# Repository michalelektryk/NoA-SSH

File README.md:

# Noise of Antimatter - Subshaper
## disclaimer
This repository contains all files required to make or repair the SSH. The following files are provided as is, with no responsibility. They're provided for personal use only. If you'd like to sell anything made out of them feel free to ping me, I'm mostly ok, as long as you're not big company scamming small manufacturers :)
## Module description
SSH is 16HP triple waveshaper with subharmonicon and sequencer. It's versatile tool for enriching sound sources and animating voices. More information can be found on [the webpage](https://noiseofantimatter.com/modules/ssh_module/) or by checking out [the demo](https://www.youtube.com/watch?v=Nd7Cz19s0W0).

## File structure
- electronics design can be found in folder [electronics](/electronics)
  - schematic.pdf is useful for quick look. For editing and deep dive full kicad design is provided. Project was done in kicad 6 but seems to work equally well in 7/8
- CPDL firmware is provided in folder [greenpak](/greenpak)
  - the device hides all complex digital logic into two greenpak CPLDs.
  - Their configuration and ESP32 software used for flashing are here
- panel design can be found in folder [panel](/panel)
  - panel has been designed as 3d model in openSCAD. Two projections are available for CNC production. Additionally, stls for dual color printing are provided
- manual generating files and pdf can be found in [manual](/manual)
  - It's written in LaTeX. For people who don't know LaTeX I recommend you read about it, especially if you're doing group projects and need to git proper documents

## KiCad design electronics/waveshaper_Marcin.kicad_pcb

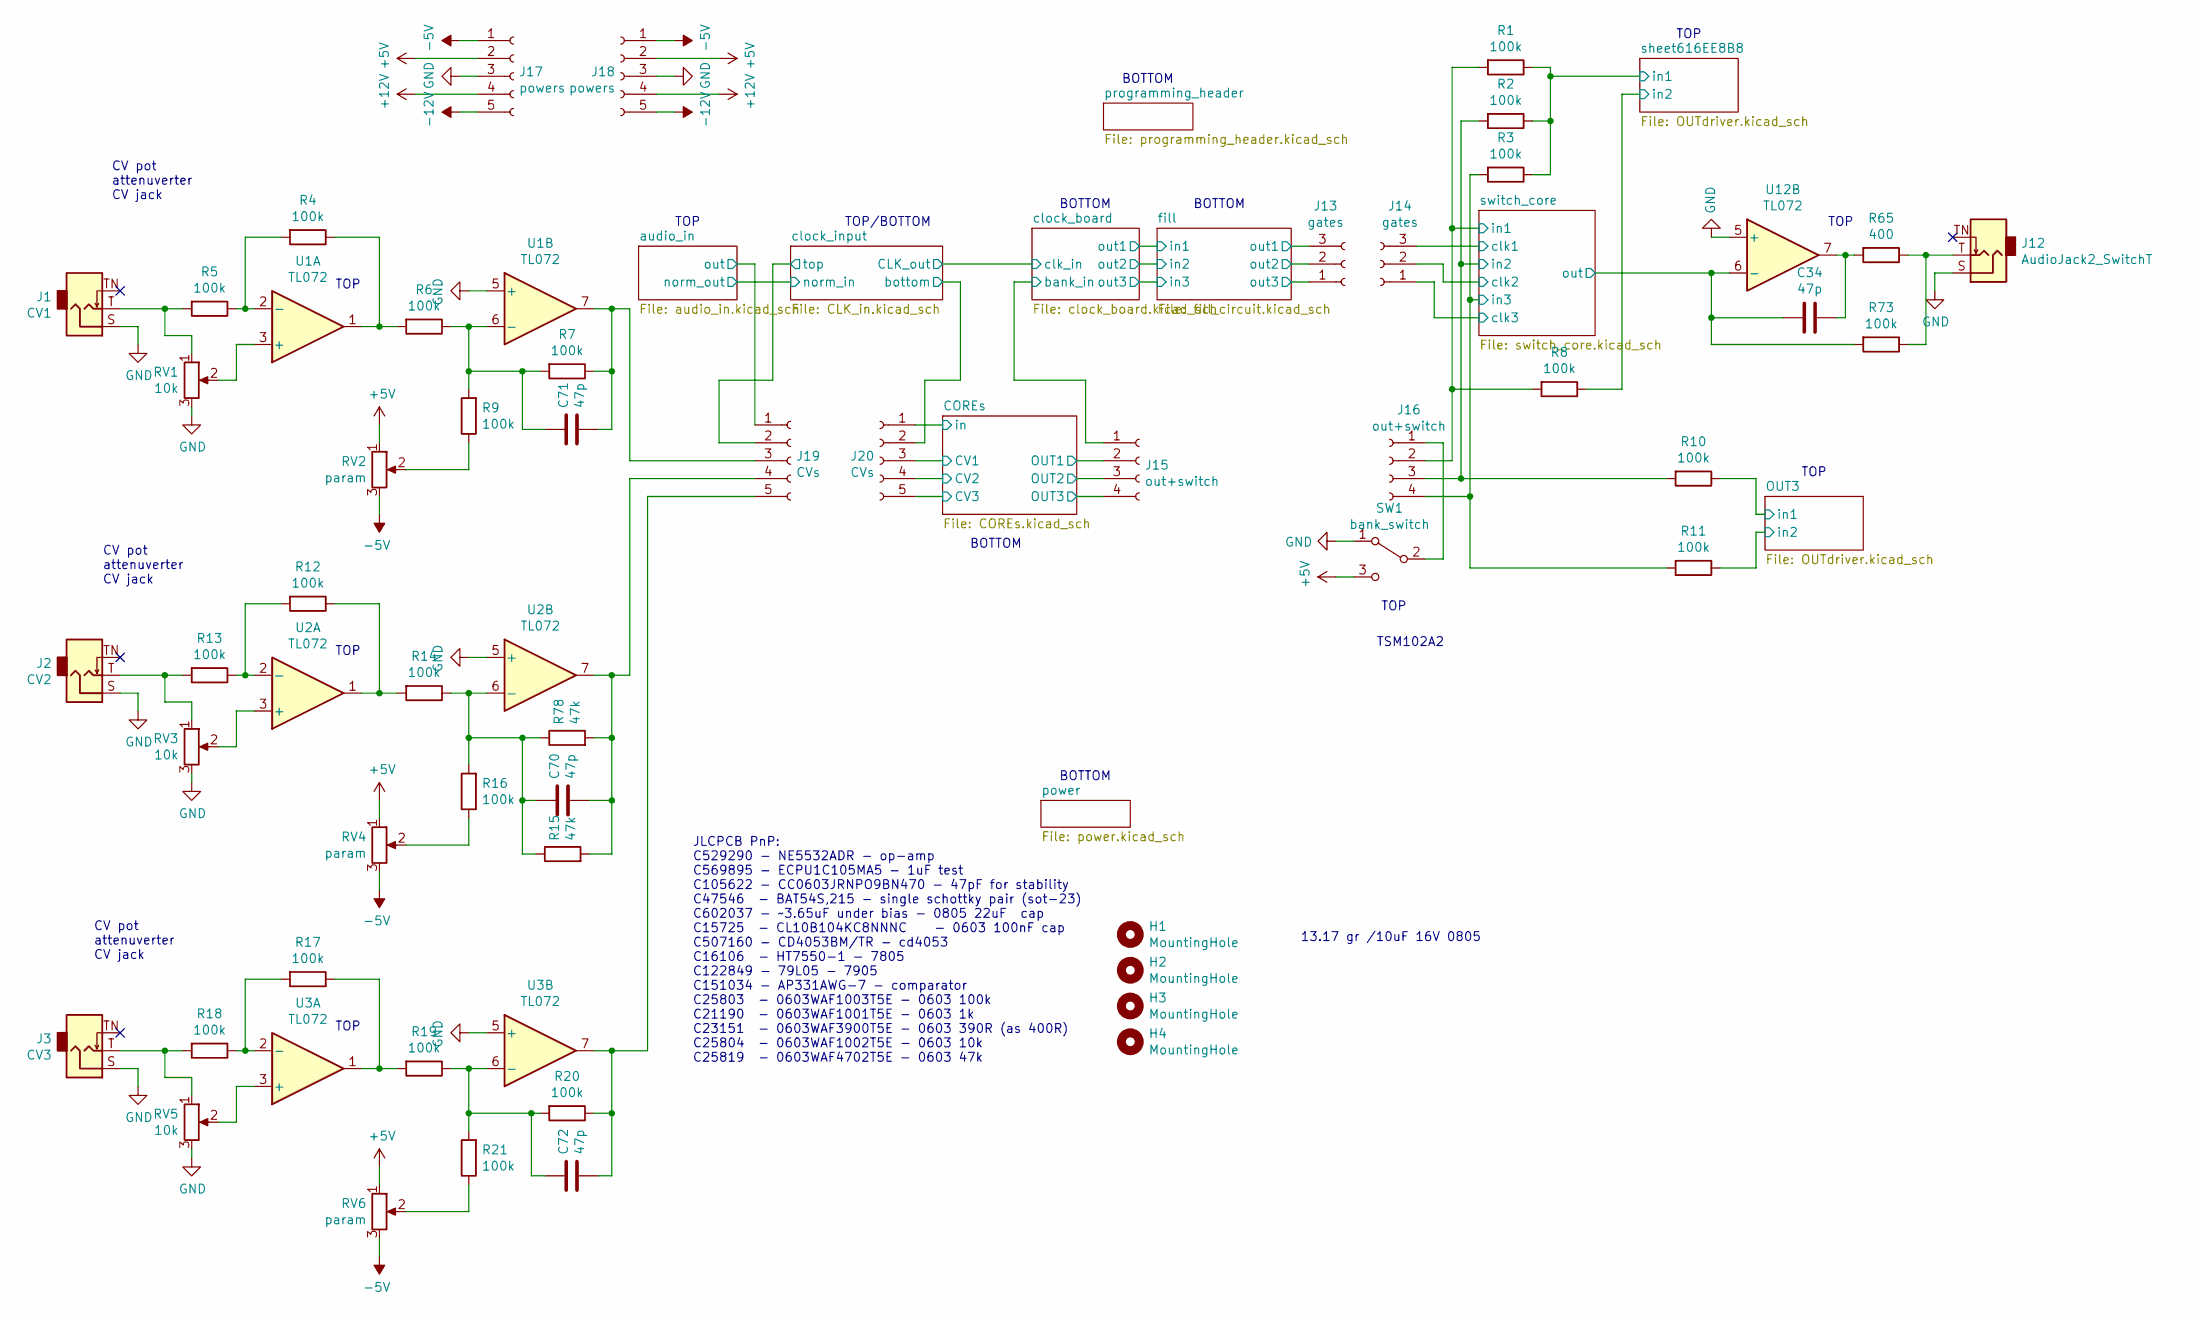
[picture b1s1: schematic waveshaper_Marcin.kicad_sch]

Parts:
C34, C70, C71, C72: 47p; C_0603_1608Metric
H1, H2, H3, H4: MountingHole; SS-16F03_cutout
J1: CV1; thonkiconn
J2: CV2; thonkiconn
J3: CV3; thonkiconn
J12: AudioJack2_SwitchT; thonkiconn
J13, J14: gates; PinHeader_1x03_P2.54mm_Vertical
J15, J16: out+switch; PinHeader_1x04_P2.54mm_Vertical
J17, J18: powers; PinHeader_1x05_P2.54mm_Vertical
J19, J20: CVs; PinHeader_1x05_P2.54mm_Vertical
R1, R2, R3, R4, R5, R6, R7, R8, R9, R10, R11, R12, R13, R14, R16, R17, R18, R19, R20, R21, R73: 100k; R_0603_1608Metric
R15, R78: 47k; R_0603_1608Metric
R65: 400; R_0603_1608Metric
RV1, RV3, RV5: 10k; Potentiometer_Alps_RK09K_Single_Vertical
RV2, RV4, RV6: param; Potentiometer_Alps_RK09K_Single_Vertical
SW1: bank_switch; TSM1x3
U1, U2, U3, U12: TL072; SOIC-8_3.9x4.9mm_P1.27mm

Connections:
+5V: J17.2, J18.2, RV2.1, RV4.1, RV6.1, SW1.3 (C); also elsewhere on the board
+12V: J17.4, J18.4; also elsewhere on the board
-5V: J17.1, J18.1, RV2.3, RV4.3, RV6.3; also elsewhere on the board
-12V: J17.5, J18.5; also elsewhere on the board
/COREs/CV1: J20.3; also elsewhere on the board
/COREs/CV2: J20.4; also elsewhere on the board
/COREs/CV3: J20.5; also elsewhere on the board
/COREs/OUT1: J15.2; also elsewhere on the board
/COREs/OUT2: J15.3; also elsewhere on the board
/COREs/OUT3: J15.4; also elsewhere on the board
/COREs/in: J20.1; also elsewhere on the board
/OUT3/in1: R10.1; also elsewhere on the board
/OUT3/in2: R11.1; also elsewhere on the board
/audio_in/out: J19.1; also elsewhere on the board
/clock_board/bank_in: J15.1; also elsewhere on the board
/clock_input/bottom: J20.2; also elsewhere on the board
/clock_input/top: J19.2; also elsewhere on the board
/fill/out1: J13.3; also elsewhere on the board
/fill/out2: J13.2; also elsewhere on the board
/fill/out3: J13.1; also elsewhere on the board
/sheet616EE8B8/in1: R1.1, R2.1, R3.1; also elsewhere on the board
/sheet616EE8B8/in2: R8.1; also elsewhere on the board
/switch_core/clk1: J14.3; also elsewhere on the board
/switch_core/clk2: J14.2; also elsewhere on the board
/switch_core/clk3: J14.1; also elsewhere on the board
/switch_core/in1: J16.2, R1.2, R8.2; also elsewhere on the board
/switch_core/in2: J16.3, R2.2, R10.2; also elsewhere on the board
/switch_core/in3: J16.4, R3.2, R11.2; also elsewhere on the board
/switch_core/out: C34.2, R73.2, U12.6 (-); also elsewhere on the board
GND: J1.S, J2.S, J3.S, J12.S, J17.3, J18.3, RV1.3, RV3.3, RV5.3, SW1.1 (A), U1.5 (+), U2.5 (+), U3.5 (+), U12.5 (+); also elsewhere on the board
unnamed: C34.1, R65.2, U12.7
unnamed: C70.1, R14.1, R15.1, R16.2, R78.1, U2.6 (-)
unnamed: C70.2, J19.4, R15.2, R78.2, U2.7
unnamed: C71.1, R6.1, R7.2, R9.2, U1.6 (-)
unnamed: C71.2, J19.3, R7.1, U1.7
unnamed: C72.1, R19.1, R20.2, R21.2, U3.6 (-)
unnamed: C72.2, J19.5, R20.1, U3.7
unnamed: J1.T, R5.2, RV1.1
unnamed: J2.T, R13.2, RV3.1
unnamed: J3.T, R18.2, RV5.1
unnamed: J12.T, R65.1, R73.1
unnamed: J16.1, SW1.2 (B)
unnamed: R4.1, R6.2, U1.1
unnamed: R4.2, R5.1, U1.2 (-)
unnamed: R9.1, RV2.2
unnamed: R12.1, R14.2, U2.1
unnamed: R12.2, R13.1, U2.2 (-)
unnamed: R16.1, RV4.2
unnamed: R17.1, R19.2, U3.1
unnamed: R17.2, R18.1, U3.2 (-)
unnamed: R21.1, RV6.2
unnamed: RV1.2, U1.3 (+)
unnamed: RV3.2, U2.3 (+)
unnamed: RV5.2, U3.3 (+)

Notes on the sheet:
CV pot attenuverter CV jack
TOP
JLCPCB PnP: C529290 - NE5532ADR - op-amp C569895 - ECPU1C105MA5 - 1uF test C105622 - CC0603JRNPO9BN470 - 47pF for stability C47546 - BAT54S,215 - single schottky pair (sot-23) C602037 - ~3.65uF under bias - 0805 22uF cap C15725 - CL10B104KC8NNNC - 0603 100nF cap C507160 - CD4053BM/TR - cd4053 C1610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
BOTTOM
13.17 gr /10uF 16V 0805
TOP/BOTTOM
TSM102A2

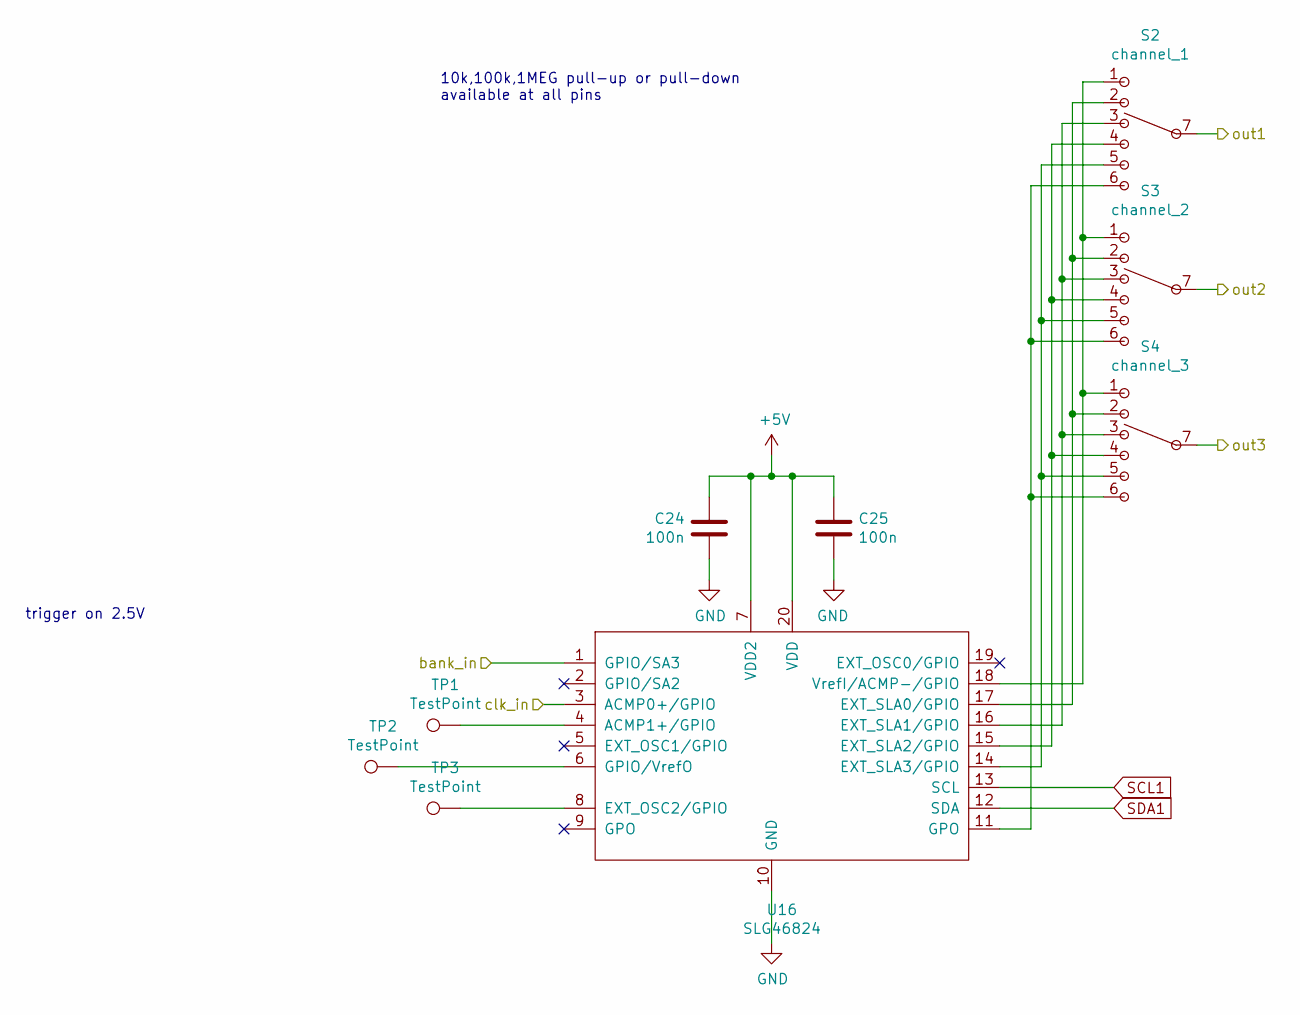
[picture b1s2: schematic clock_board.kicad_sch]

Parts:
C24, C25: 100n; C_0603_1608Metric
S2: channel_1; SS-16F03
S3: channel_2; SS-16F03
S4: channel_3; SS-16F03
TP1, TP2, TP3: TestPoint; TestPoint_Pad_D2.0mm
U16: SLG46824; TSSOP-20_4.4x6.5mm_P0.65mm

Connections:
+5V: C24.1, C25.1, U16.7 (VDD2), U16.20 (VDD); also elsewhere on the board
/clock_board/bank_in: U16.1 (GPIO/SA3); also elsewhere on the board
/clock_board/clk_in: U16.3 (ACMP0+/GPIO); also elsewhere on the board
/clock_board/out1: S2.7; also elsewhere on the board
/clock_board/out2: S3.7; also elsewhere on the board
/clock_board/out3: S4.7; also elsewhere on the board
GND: C24.2, C25.2, U16.10 (GND); also elsewhere on the board
unnamed: S2.1, S3.1, S4.1, U16.18 (VrefI/ACMP-/GPIO)
unnamed: S2.2, S3.2, S4.2, U16.17 (EXT_SLA0/GPIO)
unnamed: S2.3, S3.3, S4.3, U16.16 (EXT_SLA1/GPIO)
unnamed: S2.4, S3.4, S4.4, U16.15 (EXT_SLA2/GPIO)
unnamed: S2.5, S3.5, S4.5, U16.14 (EXT_SLA3/GPIO)
unnamed: S2.6, S3.6, S4.6, U16.11 (GPO)
unnamed: TP1.1, U16.4 (ACMP1+/GPIO)
unnamed: TP2.1, U16.6 (GPIO/VrefO)
unnamed: TP3.1, U16.8 (EXT_OSC2/GPIO)
SCL1: U16.13 (SCL); also elsewhere on the board
SDA1: U16.12 (SDA); also elsewhere on the board

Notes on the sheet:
trigger on 2.5V
10k,100k,1MEG pull-up or pull-down available at all pins

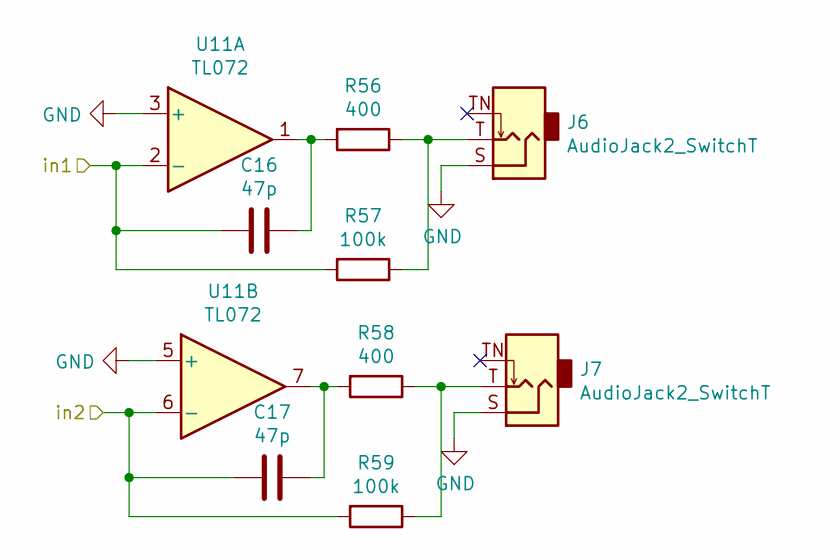
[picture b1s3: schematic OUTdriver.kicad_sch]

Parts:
C16, C17: 47p; C_0603_1608Metric
J6, J7: AudioJack2_SwitchT; thonkiconn
R56, R58: 400; R_0603_1608Metric
R57, R59: 100k; R_0603_1608Metric
U11: TL072; SOIC-8_3.9x4.9mm_P1.27mm

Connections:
/sheet616EE8B8/in1: C16.2, R57.2, U11.2 (-); also elsewhere on the board
/sheet616EE8B8/in2: C17.2, R59.2, U11.6 (-); also elsewhere on the board
GND: J6.S, J7.S, U11.3 (+), U11.5 (+); also elsewhere on the board
unnamed: C16.1, R56.2, U11.1
unnamed: C17.1, R58.2, U11.7
unnamed: J6.T, R56.1, R57.1
unnamed: J7.T, R58.1, R59.1

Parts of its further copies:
C22, C23: 47p; C_0603_1608Metric
J10, J11: AudioJack2_SwitchT; thonkiconn
R68, R70: 400; R_0603_1608Metric
R69, R71: 100k; R_0603_1608Metric

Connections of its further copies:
/OUT3/in1: C22.2, R69.2; also elsewhere on the board
/OUT3/in2: C23.2, R71.2; also elsewhere on the board
GND: J10.S, J11.S; also elsewhere on the board
unnamed 43: C22.1, R68.2; also elsewhere on the board
unnamed 44: C23.1, R70.2; also elsewhere on the board
unnamed: J10.T, R68.1, R69.1
unnamed: J11.T, R70.1, R71.1

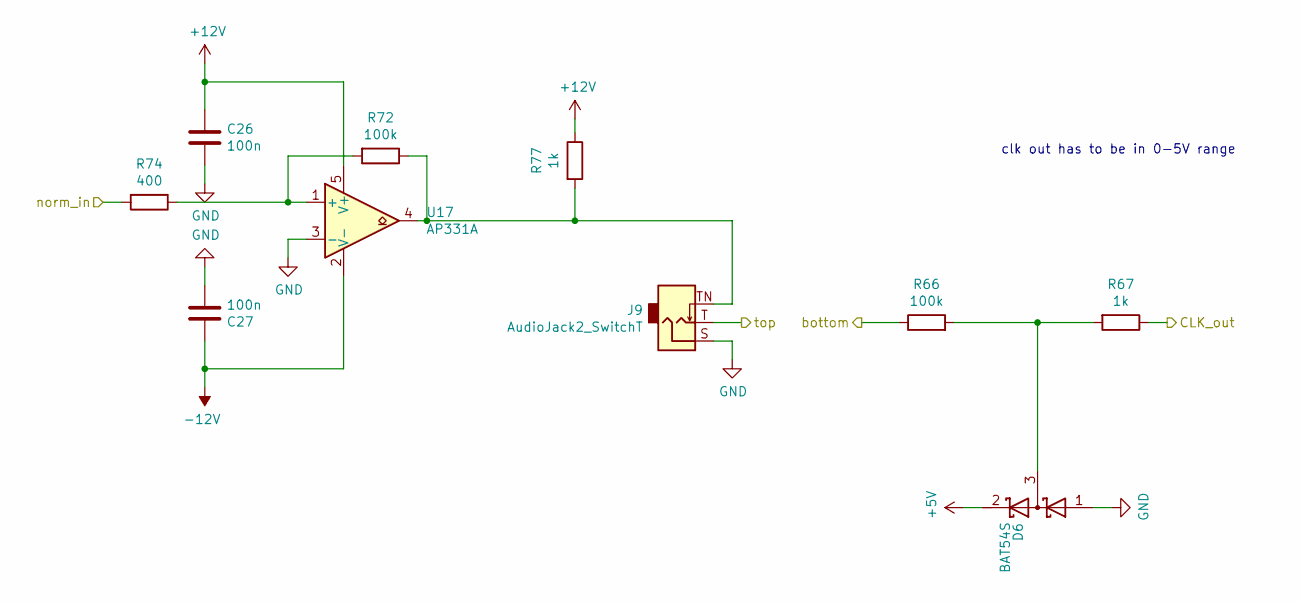
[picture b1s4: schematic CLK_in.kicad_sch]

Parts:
C26, C27: 100n; C_0603_1608Metric
D6: BAT54S; SOT-23
J9: AudioJack2_SwitchT; thonkiconn
R66, R72: 100k; R_0603_1608Metric
R67, R77: 1k; R_0603_1608Metric
R74: 400; R_0603_1608Metric
U17: AP331A; SOT-23-5

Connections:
+5V: D6.2 (K); also elsewhere on the board
+12V: C26.1, R77.1, U17.5 (V+); also elsewhere on the board
-12V: C27.1, U17.2 (V-); also elsewhere on the board
/audio_in/norm_out: R74.2; also elsewhere on the board
/clock_board/clk_in: R67.1; also elsewhere on the board
/clock_input/bottom: R66.1; also elsewhere on the board
/clock_input/top: J9.T; also elsewhere on the board
GND: C26.2, C27.2, D6.1 (A), J9.S, U17.3 (-); also elsewhere on the board
unnamed: D6.3 (common), R66.2, R67.2
unnamed: J9.TN, R72.1, R77.2, U17.4
unnamed: R72.2, R74.1, U17.1 (+)

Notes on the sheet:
clk out has to be in 0-5V range

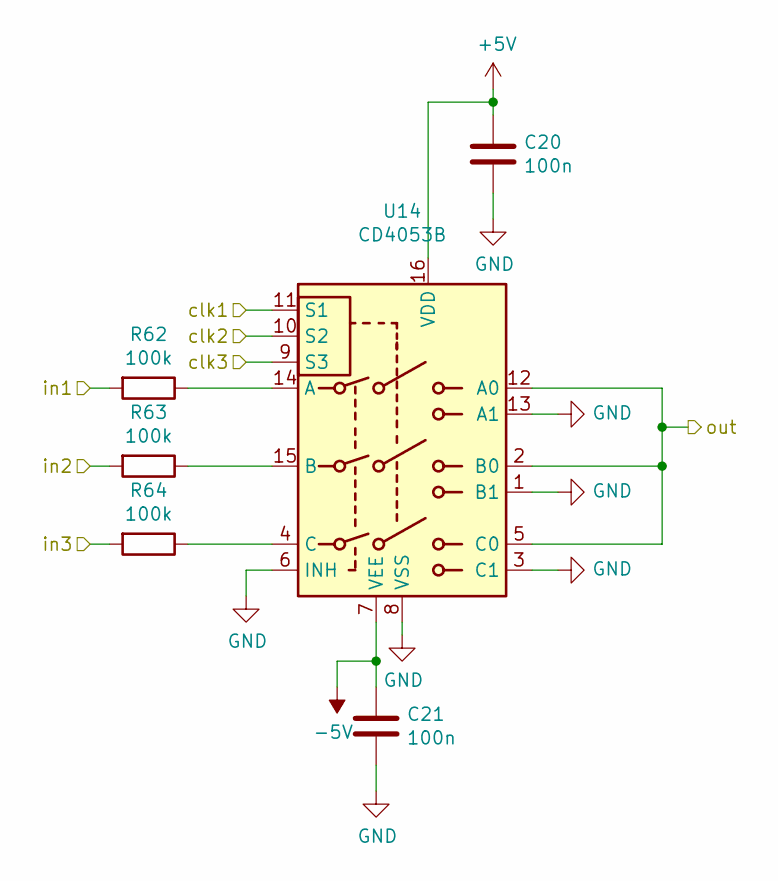
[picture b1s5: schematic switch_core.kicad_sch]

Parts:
C20, C21: 100n; C_0603_1608Metric
R62, R63, R64: 100k; R_0603_1608Metric
U14: CD4053B; SOP-16_3.9x9.9mm_P1.27mm

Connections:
+5V: C20.1, U14.16 (VDD); also elsewhere on the board
-5V: C21.1, U14.7 (VEE); also elsewhere on the board
/switch_core/clk1: U14.11 (S1); also elsewhere on the board
/switch_core/clk2: U14.10 (S2); also elsewhere on the board
/switch_core/clk3: U14.9 (S3); also elsewhere on the board
/switch_core/in1: R62.2; also elsewhere on the board
/switch_core/in2: R63.2; also elsewhere on the board
/switch_core/in3: R64.2; also elsewhere on the board
/switch_core/out: U14.2 (B0), U14.5 (C0), U14.12 (A0); also elsewhere on the board
GND: C20.2, C21.2, U14.1 (B1), U14.3 (C1), U14.6 (INH), U14.8 (VSS), U14.13 (A1); also elsewhere on the board
unnamed: R62.1, U14.14 (A)
unnamed: R63.1, U14.15 (B)
unnamed: R64.1, U14.4 (C)

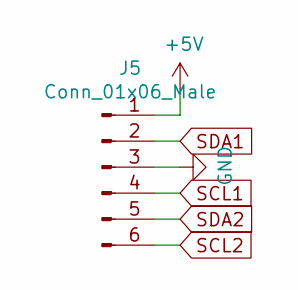
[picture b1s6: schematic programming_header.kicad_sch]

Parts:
J5: Conn_01x06_Male; PinHeader_2x03_P2.00mm_Vertical

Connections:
+5V: J5.1; also elsewhere on the board
GND: J5.3; also elsewhere on the board
SCL1: J5.4; also elsewhere on the board
SCL2: J5.6; also elsewhere on the board
SDA1: J5.2; also elsewhere on the board
SDA2: J5.5; also elsewhere on the board

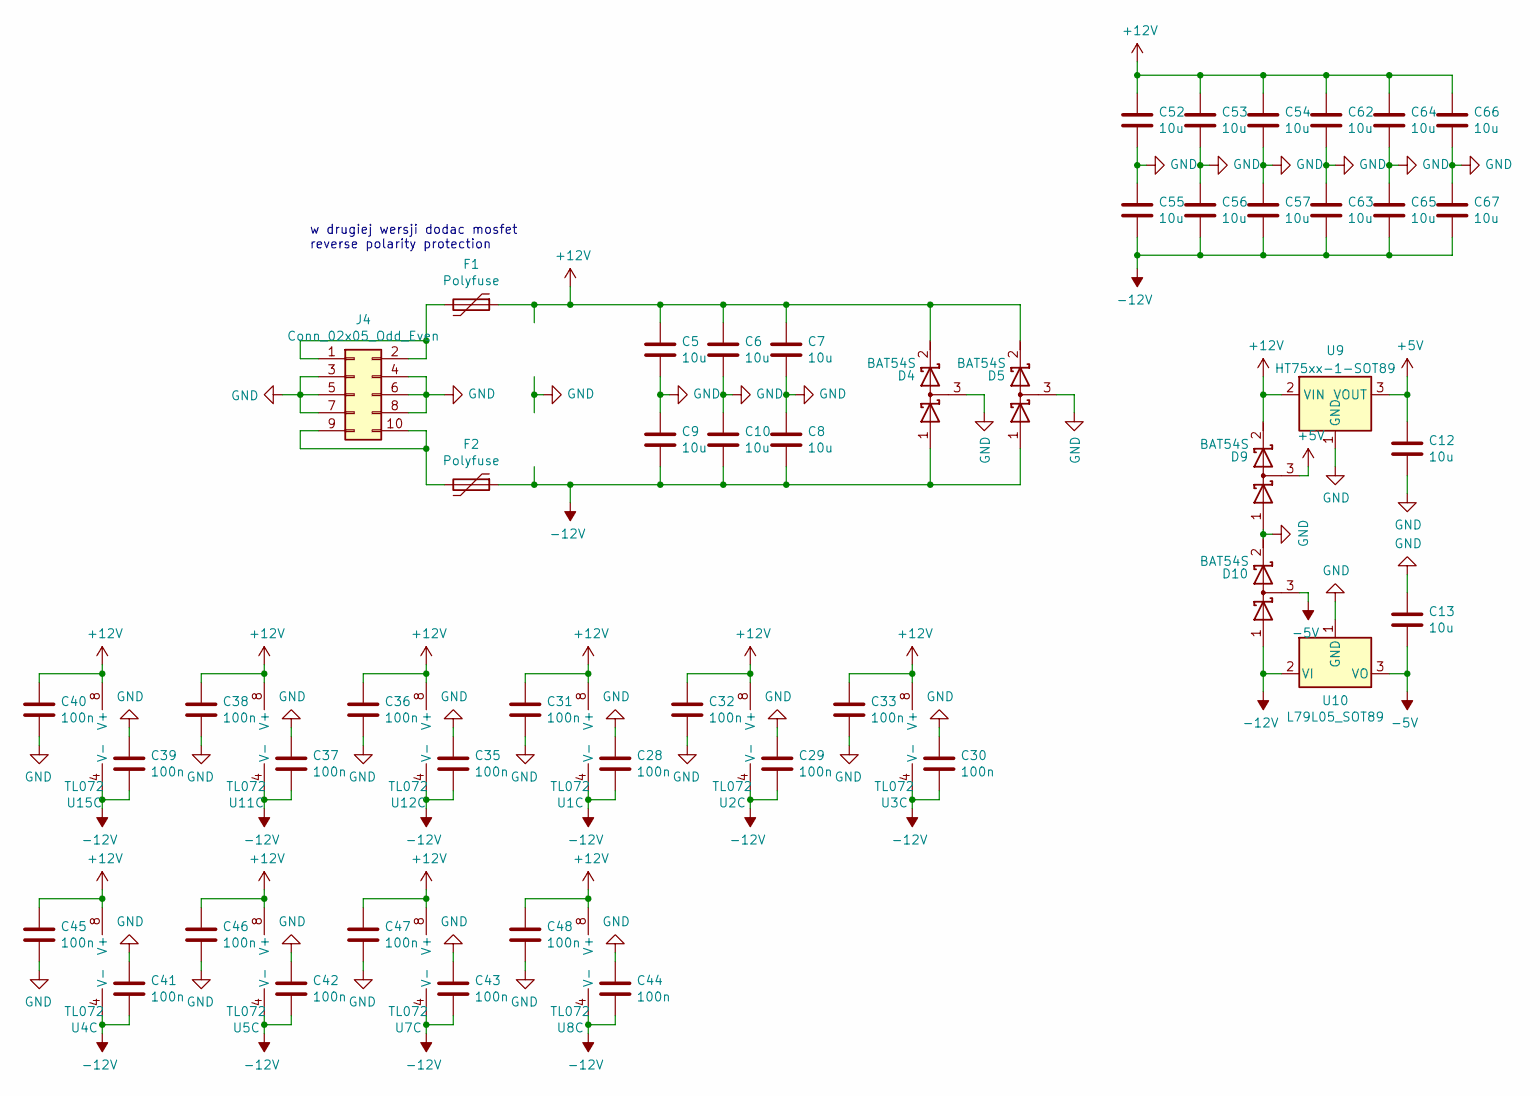
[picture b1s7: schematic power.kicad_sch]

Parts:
C5, C6, C7, C8, C9, C10, C12, C13, C52, C53, C54, C55, C56, C57, C62, C63, C64, C65, C66, C67: 10u; C_0805_2012Metric
C28, C29, C30, C31, C32, C33, C35, C36, C37, C38, C39, C40, C41, C42, C43, C44, C45, C46, C47, C48: 100n; C_0603_1608Metric
D4, D5, D9, D10: BAT54S; SOT-23
F1, F2: Polyfuse; Fuse_0805_2012Metric
J4: Conn_02x05_Odd_Even; PinHeader_2x05_P2.54mm_Vertical_SMD
U1, U2, U3, U4, U5, U7, U8, U11, U12, U15: TL072; SOIC-8_3.9x4.9mm_P1.27mm
U9: HT75xx-1-SOT89; SOT-89-3
U10: L79L05_SOT89; SOT-89-3

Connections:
+5V: C12.1, D9.3 (common), U9.3 (VOUT); also elsewhere on the board
+12V: C5.1, C6.1, C7.1, C31.1, C32.1, C33.1, C36.1, C38.1, C40.1, C45.1, C46.1, C47.1, C48.1, C52.1, C53.1, C54.1, C62.1, C64.1, C66.1, D4.2 (K), D5.2 (K), D9.2 (K), F1.1, U1.8 (V+), U2.8 (V+), U3.8 (V+), U4.8 (V+), U5.8 (V+), U7.8 (V+), U8.8 (V+), U9.2 (VIN), U11.8 (V+), U12.8 (V+), U15.8 (V+); also elsewhere on the board
-5V: C13.2, D10.3 (common), U10.3 (VO); also elsewhere on the board
-12V: C8.2, C9.2, C10.2, C28.2, C29.2, C30.2, C35.2, C37.2, C39.2, C41.2, C42.2, C43.2, C44.2, C55.2, C56.2, C57.2, C63.2, C65.2, C67.2, D4.1 (A), D5.1 (A), D10.1 (A), F2.1, U1.4 (V-), U2.4 (V-), U3.4 (V-), U4.4 (V-), U5.4 (V-), U7.4 (V-), U8.4 (V-), U10.2 (VI), U11.4 (V-), U12.4 (V-), U15.4 (V-); also elsewhere on the board
GND: C5.2, C6.2, C7.2, C8.1, C9.1, C10.1, C12.2, C13.1, C28.1, C29.1, C30.1, C31.2, C32.2, C33.2, C35.1, C36.2, C37.1, C38.2, C39.1, C40.2, C41.1, C42.1, C43.1, C44.1, C45.2, C46.2, C47.2, C48.2, C52.2, C53.2, C54.2, C55.1, C56.1, C57.1, C62.2, C63.1, C64.2, C65.1, C66.2, C67.1, D4.3 (common), D5.3 (common), D9.1 (A), D10.2 (K), J4.3, J4.4, J4.5, J4.6, J4.7, J4.8, U9.1 (GND), U10.1 (GND); also elsewhere on the board
unnamed: F1.2, J4.1, J4.2
unnamed: F2.2, J4.9, J4.10

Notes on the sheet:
w drugiej wersji dodac mosfet reverse polarity protection

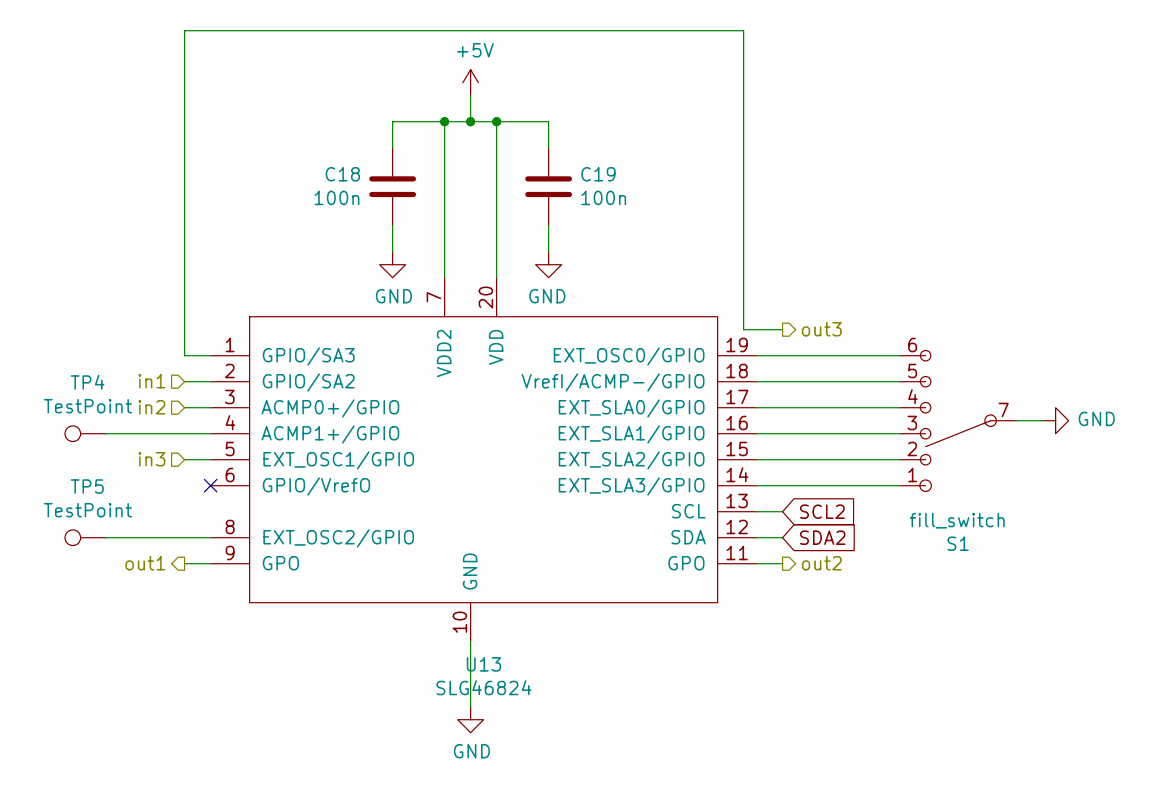
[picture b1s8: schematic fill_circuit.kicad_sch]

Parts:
C18, C19: 100n; C_0603_1608Metric
S1: fill_switch; SS-16F03
TP4, TP5: TestPoint; TestPoint_Pad_D2.0mm
U13: SLG46824; TSSOP-20_4.4x6.5mm_P0.65mm

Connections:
+5V: C18.1, C19.1, U13.7 (VDD2), U13.20 (VDD); also elsewhere on the board
/clock_board/out1: U13.2 (GPIO/SA2); also elsewhere on the board
/clock_board/out2: U13.3 (ACMP0+/GPIO); also elsewhere on the board
/clock_board/out3: U13.5 (EXT_OSC1/GPIO); also elsewhere on the board
/fill/out1: U13.9 (GPO); also elsewhere on the board
/fill/out2: U13.11 (GPO); also elsewhere on the board
/fill/out3: U13.1 (GPIO/SA3); also elsewhere on the board
GND: C18.2, C19.2, S1.7, U13.10 (GND); also elsewhere on the board
unnamed: S1.1, U13.14 (EXT_SLA3/GPIO)
unnamed: S1.2, U13.15 (EXT_SLA2/GPIO)
unnamed: S1.3, U13.16 (EXT_SLA1/GPIO)
unnamed: S1.4, U13.17 (EXT_SLA0/GPIO)
unnamed: S1.5, U13.18 (VrefI/ACMP-/GPIO)
unnamed: S1.6, U13.19 (EXT_OSC0/GPIO)
unnamed: TP4.1, U13.4 (ACMP1+/GPIO)
unnamed: TP5.1, U13.8 (EXT_OSC2/GPIO)
SCL2: U13.13 (SCL); also elsewhere on the board
SDA2: U13.12 (SDA); also elsewhere on the board

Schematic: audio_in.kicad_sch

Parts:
J8: AudioJack2_SwitchT; thonkiconn
R60, R61: 100k; R_0603_1608Metric
RV8: gain; Potentiometer_Alps_RK09K_Single_Vertical
U12: TL072; SOIC-8_3.9x4.9mm_P1.27mm

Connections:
/audio_in/norm_out: R61.1, RV8.1, U12.1; also elsewhere on the board
/audio_in/out: RV8.2; also elsewhere on the board
GND: J8.S, RV8.3, U12.3 (+); also elsewhere on the board
unnamed: J8.T, R60.2
unnamed: R60.1, R61.2, U12.2 (-)

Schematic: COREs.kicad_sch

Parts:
C1, C2: 100n; C_0603_1608Metric
C3, C58, C59, C60, C61: 1u - test; C_1210_3225Metric
C14, C15, C49, C50, C51, C68, C69: 47p; C_0603_1608Metric
D1, D2, D3, D7, D8: BAT54S; SOT-23
JP1, JP2, JP3, JP4, JP5: Jumper; SolderJumper-2_P1.3mm_Open_RoundedPad1.0x1.5mm
R22, R23, R26, R33, R34, R35, R36, R47, R48, R49, R50, R51, R52, R53, R54: 100k; R_0603_1608Metric
R24, R25, R31, R40, R41, R42, R44, R45, R55, R75, R76: 10k; R_0603_1608Metric
R27, R28, R29, R30, R32, R37, R46: 1k; R_0603_1608Metric
R38, R39: 47k; R_0603_1608Metric
R43: 250k; R_0603_1608Metric
U4, U5, U7, U8: TL072; SOIC-8_3.9x4.9mm_P1.27mm
U6: AS3363; SOIC-16_3.9x9.9mm_P1.27mm

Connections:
+5V: R75.2; also elsewhere on the board
+12V: C1.1, U6.16 (Vcc); also elsewhere on the board
-5V: R40.2; also elsewhere on the board
-12V: C2.1, U6.8 (Vee); also elsewhere on the board
/COREs/CV1: R25.2; also elsewhere on the board
/COREs/CV2: R37.1; also elsewhere on the board
/COREs/CV3: D3.3 (common), R38.1; also elsewhere on the board
/COREs/OUT1: JP1.2; also elsewhere on the board
/COREs/OUT2: JP3.1; also elsewhere on the board
/COREs/OUT3: JP2.2; also elsewhere on the board
/COREs/in: D7.3 (common), JP4.2, JP5.2, R31.1, R50.1; also elsewhere on the board
GND: C1.2, C2.2, D2.3 (common), R26.2, R27.2, R28.1, R29.1, R30.1, R41.2, R44.2, R45.1, R46.2, R54.2, R76.2, U4.3 (+), U5.3 (+), U5.5 (+), U6.1 (GND), U7.3 (+), U8.3 (+), U8.5 (+); also elsewhere on the board
unnamed: C3.1, C50.1, C58.2, C59.1, C60.2, C61.1, R51.1, U8.1
unnamed: C3.2, C58.1, C59.2, C60.1, C61.2, R55.1
unnamed: C14.1, R22.1, R23.2, U4.6 (-)
unnamed: C14.2, R23.1, R24.2, U4.7
unnamed: C15.1, JP1.1, R34.1, U5.7
unnamed: C15.2, R34.2, U5.6 (-), U6.5 (Iout1)
unnamed: C49.1, R36.1, R47.2, U5.1
unnamed: C49.2, R36.2, U5.2 (-), U6.6 (Iout3)
unnamed: C50.2, R51.2, U6.12 (Iout2), U8.2 (-)
unnamed: C51.1, R42.2, R49.1, U7.7
unnamed: C51.2, R49.2, R53.1, U7.6 (-)
unnamed: C68.1, R47.1, R48.2, R50.2, U7.2 (-)
unnamed: C68.2, JP2.1, R48.1, U7.1
unnamed: C69.1, R52.2, R55.2, U8.6 (-)
unnamed: C69.2, JP3.2, R52.1, U8.7
unnamed: D1.1 (A), U4.1
unnamed: D1.3 (common), R24.1, R25.1, R27.1, U4.2 (-), U6.3 (CVMix1)
unnamed: D2.1 (A), D2.2 (K), R31.2, R32.1
unnamed: D3.1 (A), R53.2
unnamed: D3.2 (K), R54.1, U7.5 (+)
unnamed: D7.1 (A), R22.2
unnamed: D7.2 (K), R26.1, U4.5 (+)
unnamed: D8.1 (A), R35.1
unnamed: D8.2 (K), R33.1
unnamed: D8.3 (common), JP4.1
unnamed: JP5.1, R39.2, R43.2
unnamed: R28.2, R32.2, U6.2 (IN1)
unnamed: R29.2, R35.2, U6.10 (IN3B)
unnamed: R30.2, R33.2, U6.9 (IN3A)
unnamed: R37.2, U6.13 (Vcntrl2)
unnamed: R38.2, R44.1, U6.11 (CVMix3)
unnamed: R39.1, R45.2, U6.14 (CVMix2)
unnamed: R40.1, R41.1, R42.1, U6.7 (Vcntrl3)
unnamed: R43.1, R46.1, U6.15 (IN2)
unnamed: R75.1, R76.1, U6.4 (Vcntrl1)

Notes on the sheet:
CV3 needs to be +-10V
doubler circuit
X circuit
ABS circuit
CV2 needs to be +-2V

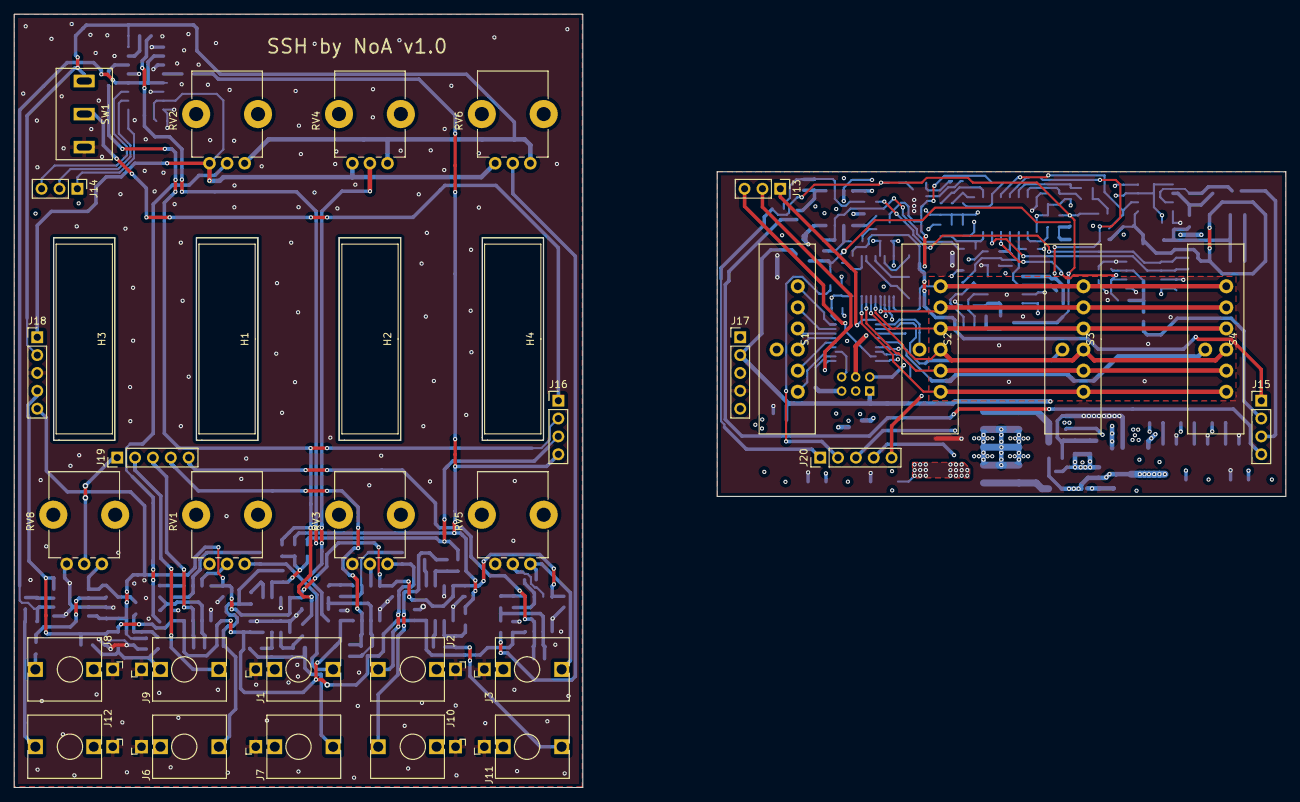
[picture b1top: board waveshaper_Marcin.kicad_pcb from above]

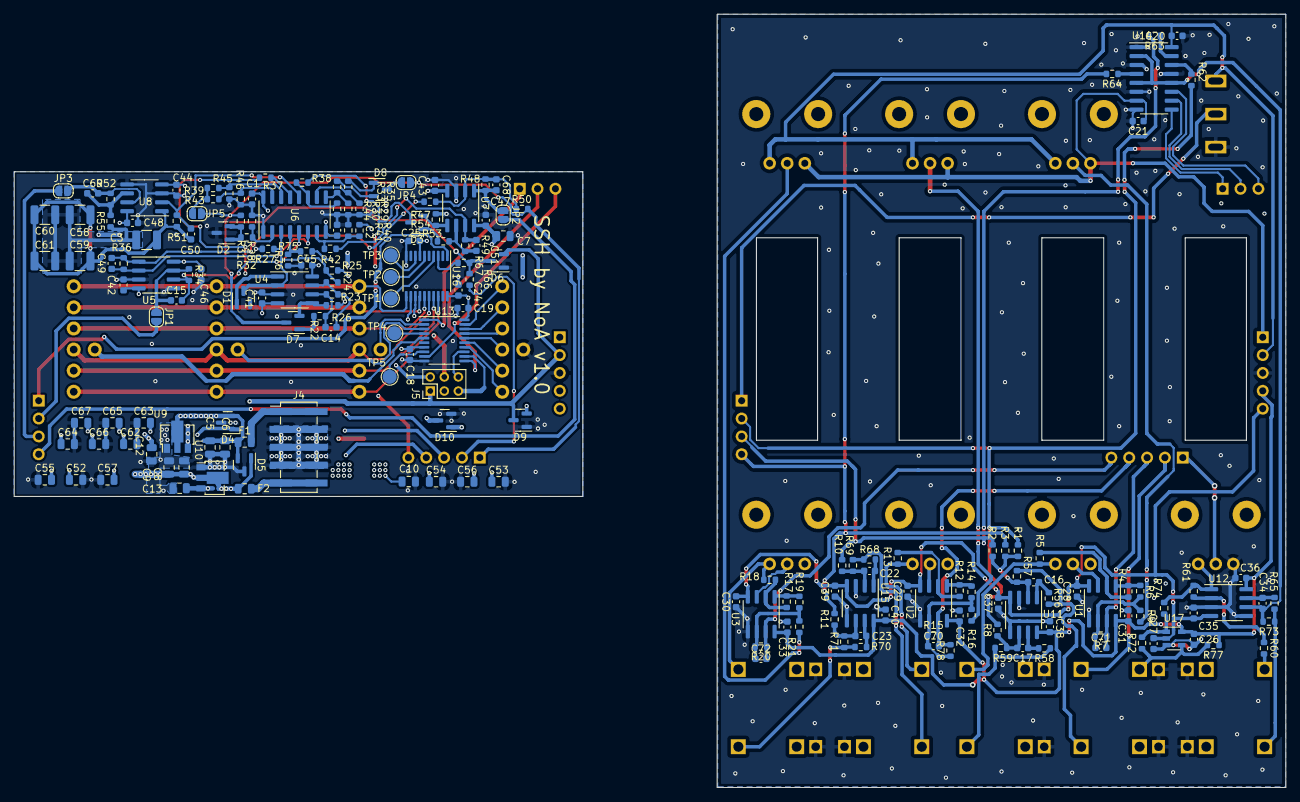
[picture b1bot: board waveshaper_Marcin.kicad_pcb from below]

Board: 4 copper layers, 180.9 x 110.0 mm, 223 parts (189 on the bottom side), 133 nets.

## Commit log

2024-05-23 documentation for public
